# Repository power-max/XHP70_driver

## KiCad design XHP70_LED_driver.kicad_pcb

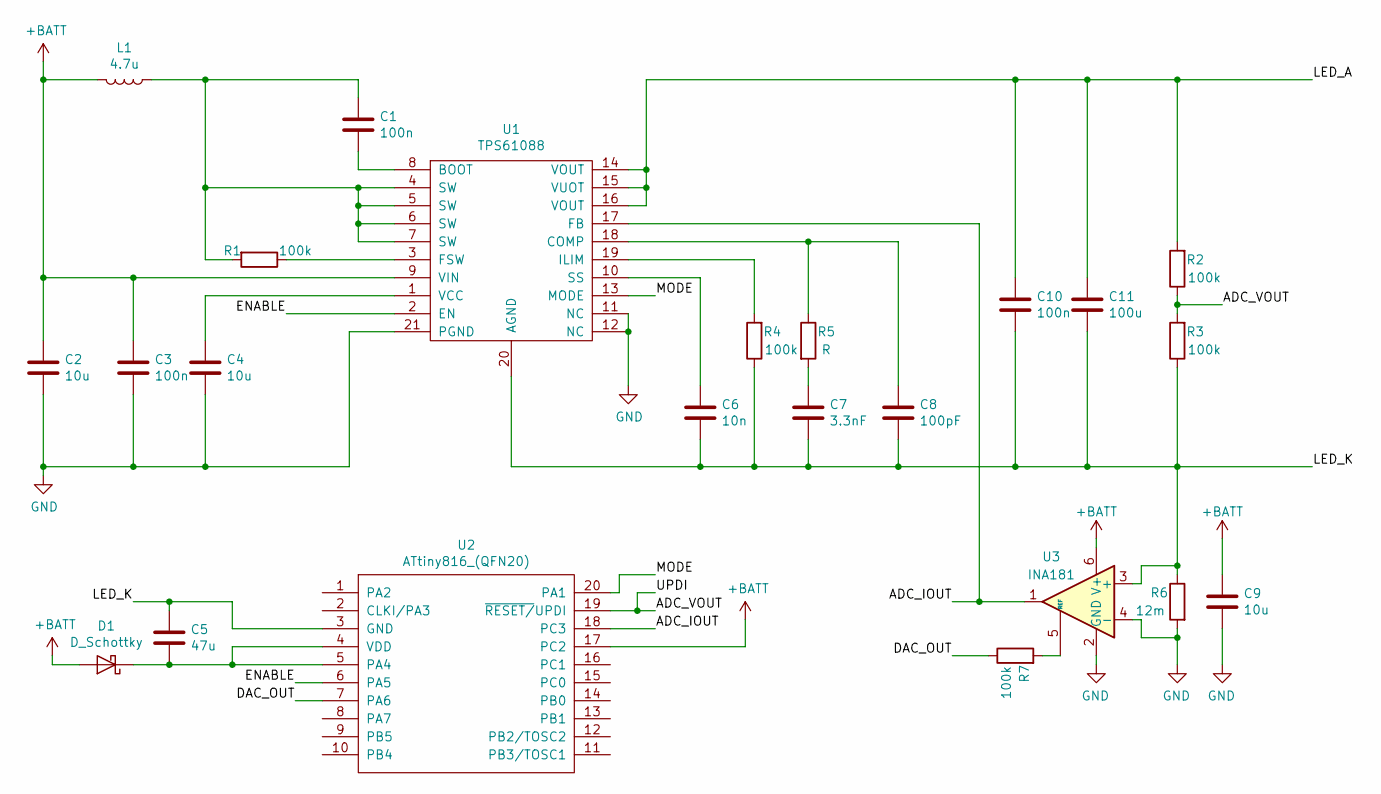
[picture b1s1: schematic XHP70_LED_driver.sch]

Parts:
C1, C3, C10: 100n; C_0402
C2: 10u; C_1210
C4, C9: 10u; C_0402
C5: 47u; C_0805
C6: 10n; C_0402
C7: 3.3nF; C_0402
C8: 100pF; C_0402
C11: 100u; C_1210
D1: D_Schottky; D_SOD-523
L1: 4.7u; L_6.3x6.3_H3
R1, R2, R3, R4, R7: 100k; R_0402_NoSilk
R5: R; R_0402_NoSilk
R6: 12m; R_0805
U1: TPS61088
U2: ATtiny816_(QFN20); UQFN-20-1EP_3x3mm_Pitch0.4mm
U3: INA181; SOT-23-6

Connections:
+BATT: C2.2, C3.2, C9.2, D1.2 (A), L1.2, U1.9 (VIN), U2.17 (PC2), U3.6 (V+)
/ADC_IOUT: U1.17 (FB), U2.18 (PC3), U3.1
/ADC_VOUT: R2.1, R3.2, U2.19 (~RESET/~UPDI)
/DAC_OUT: R7.1, U2.7 (PA6)
/ENABLE: U1.2 (EN), U2.6 (PA5)
/LED_A: C10.2, C11.2, R2.2, U1.14 (VOUT), U1.15 (VUOT), U1.16 (VOUT)
/LED_K: C5.1, C6.1, C7.1, C8.1, C10.1, C11.1, R3.1, R4.1, R6.1, U1.20 (AGND), U2.3 (GND), U3.3 (+)
/MODE: U1.13 (MODE), U2.20 (PA1)
GND: C2.1, C3.1, C4.1, C9.1, R6.2, U1.11 (NC), U1.12 (NC), U1.21 (PGND), U3.2 (GND), U3.4 (-)
unnamed: C1.1, U1.8 (BOOT)
unnamed: C1.2, L1.1, R1.2, U1.4 (SW), U1.5 (SW), U1.6 (SW), U1.7 (SW)
unnamed: C4.2, U1.1 (VCC)
unnamed: C5.2, D1.1 (K), U2.4 (VDD), U2.5 (PA4)
unnamed: C6.2, U1.10 (SS)
unnamed: C7.2, R5.2
unnamed: C8.2, R5.1, U1.18 (COMP)
unnamed: R1.1, U1.3 (FSW)
unnamed: R4.2, U1.19 (ILIM)
unnamed: R7.2, U3.5 (REF)

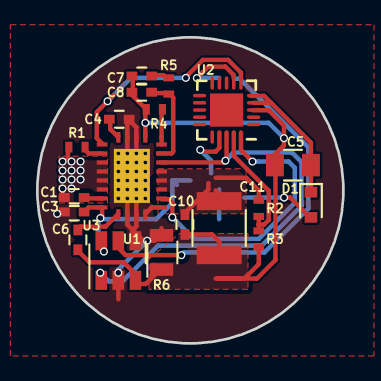
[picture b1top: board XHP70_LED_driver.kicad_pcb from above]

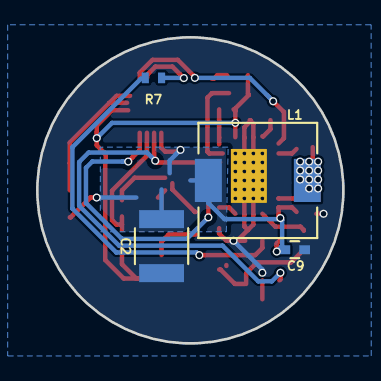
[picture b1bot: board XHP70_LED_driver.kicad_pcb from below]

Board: 2 copper layers, 17.0 x 17.0 mm, 23 parts (4 on the bottom side), 19 nets.

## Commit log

2018-12-27 added gerbers
2018-12-27 removed redundant folder
2018-12-28 added schematic PDF
2018-12-28 added custom component footprint and symbol
2019-01-02 added microcontroller
2019-01-02 exported project milestone, fixed problems
2019-01-02 finished, ready for prod.
